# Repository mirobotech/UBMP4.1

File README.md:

# UBMP4.1

UBMP4.1 (USB-Based Beginner Multipurpose Project 4 rev. 1) KiCad schematic and PCB design files.

UBMP4.1 is a development board for learning or teaching PICmicro programming in C using almost any device – including Chromebooks!

## UBMP4.1 Hardware Features

- Microchip PIC16F1459 USB-capable microcontroller with 8k words of program FLASH (6k words free when using the USB bootloader), 128B of user FLASH, 1kB of RAM, 10-bit ADC, and a built-in temperature sensor
- 5 built-in pushbuttons
- 5 visible light LEDs
- 1 piezo beeper output
- optional 8-pin header for PORTC I/O pin expansion (great for servos, a SONAR module, NeoPixels, an LCD, etc.)
- optional IR LED output for remote control transmitter applications (or a high-current transistor-driven output)
- optional IR demodulator for remote control decoding
- optional IR phototransistor or visible-light ambient light sensor for light sensing
- USB 2.0 type-C port for power and programming
- 6-pin ICSP (In-Circuit Serial Programming) header for PICkit-4

## UBMP4.1 Software Features

UBMP4.1 uses the [USB uC](https://github.com/johnnydrazzi/USB-uC) bootloader, which makes UBMP4.1 appear as a USB mass storage device. Programs can be developed in C or assembly code using Microchip Technology's MPLAB X IDE or the MPLAB Xpress web-based IDE, or in any programming language or software that creates a Microchip-compatible .hex output file.

Just plug UBMP4.1 into a USB port, wait for it to appear on your computer as drive ***PIC16F1459***, and drag your compiled .hex file onto the drive. UMBP4.1 starts running your program as soon as the .hex file is transferred.

## UMBP4.1 is Open

UBMP4.1 is open hardware and uses open source software. The following permissions and conditions apply to UBMP4.1:
- the KiCad UBMP4.1 files stored in GitHub are open hardware licensed under the terms of the MIT license (except the mirobo.tech logo - see below)
- UBMP4.1 programs stored in GitHub are open source software licensed under the terms of the MIT license
- UMBP4.1 learning materials on the mirobo.tech website are licensed under the terms of the Creative Commons CC-BY 4.0 license
- the USB uC bootloader is open source and licensed under the terms of the GPL3.0 license by John Izzard
- the mirobo.tech logo mark is a trademark of mirobo Technolgy and may not be used without prior permission

## Where can I buy UBMP4.1?

UBMP4.1 boards and kits are available at [mirobo.tech](https://mirobo.tech/ubmp4).  
Bare UBMP4.1 printed circuit boards are also available from [OSHPARK](https://oshpark.com/shared_projects/b04AabPV).

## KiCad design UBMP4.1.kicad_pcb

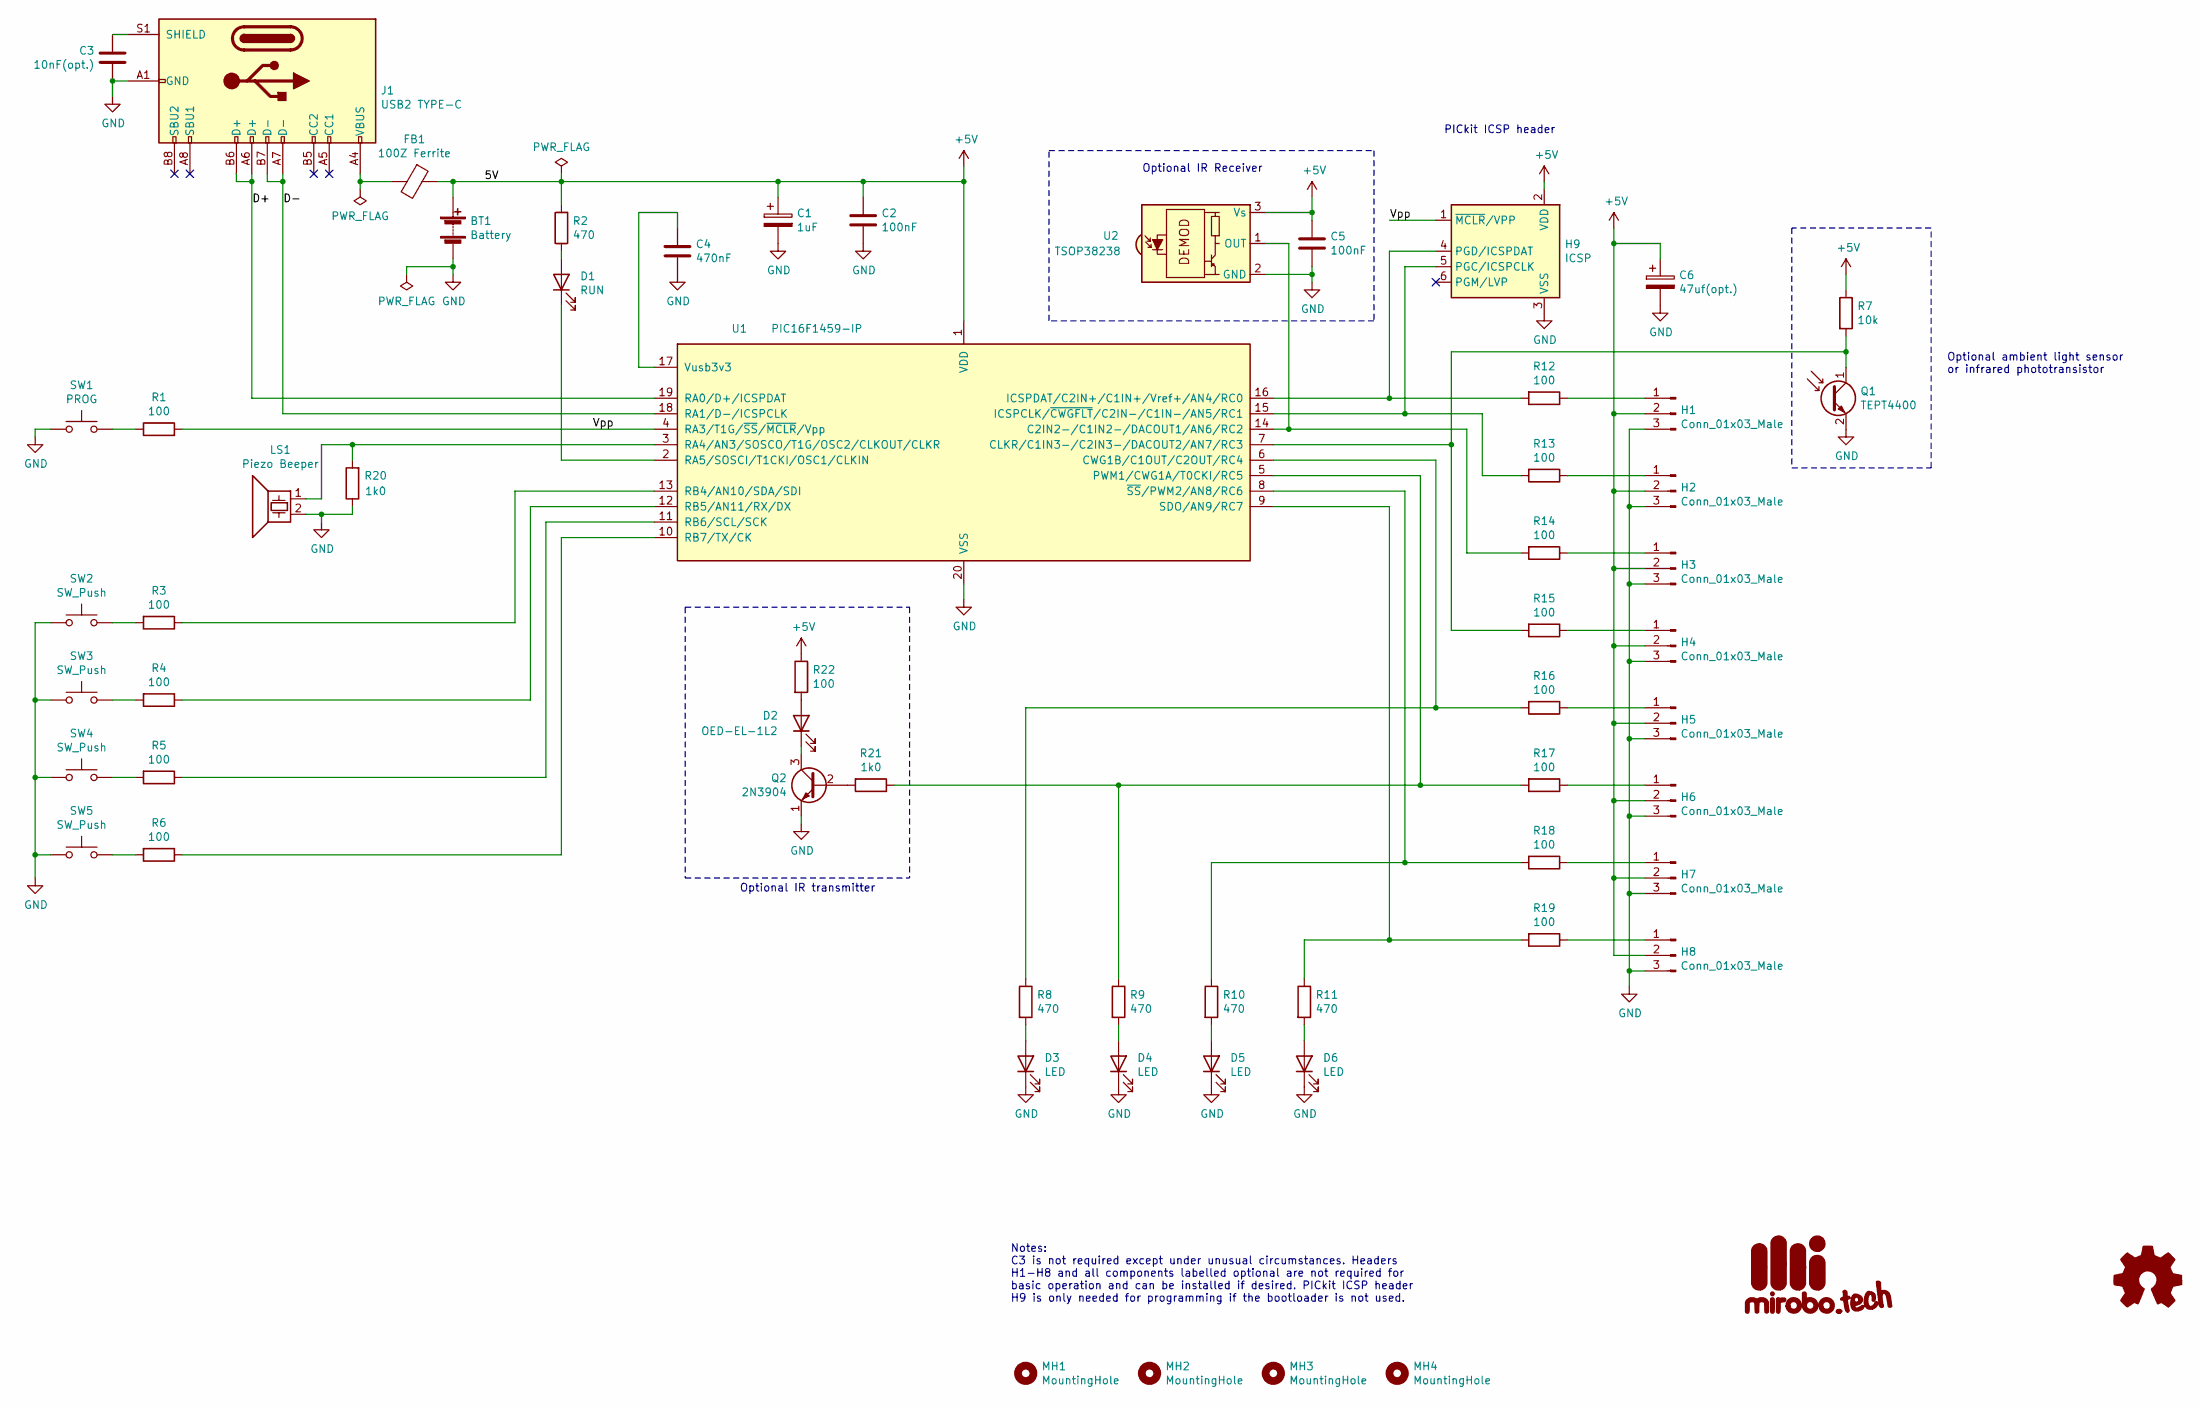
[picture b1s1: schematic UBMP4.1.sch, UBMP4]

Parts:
BT1: Battery; PinHeader_1x02_P2.54mm_Vertical
C1: 1uF; CP_Radial_D5.0mm_P2.50mm
C2, C5: 100nF; C_Disc_D3.4mm_W2.1mm_P2.50mm
C3: 10nF(opt.); C_Disc_D3.4mm_W2.1mm_P2.50mm
C4: 470nF; C_Disc_D3.4mm_W2.1mm_P2.50mm
C6: 47uf(opt.); CP_Radial_D6.3mm_P2.50mm
D1: RUN; LED_D3.0mm
D2: OED-EL-1L2; LED_D5.0mm_Horizontal_O1.27mm_Z3.0mm_Clear
D3, D4, D5, D6: LED; LED_D3.0mm
FB1: 100Z Ferrite; R_Axial_DIN0411_L9.9mm_D3.6mm_P12.70mm_Horizontal
G1: mirobotech_logo; mirobo_logo_10
G2: Logo_Open_Hardware_Small; OSHW-Symbol_6.7x6mm_SilkScreen
H1, H2, H3, H4, H5, H6, H7, H8: Conn_01x03_Male; PinHeader_1x03_P2.54mm_Vertical
H9: ICSP; PinHeader_1x06_P2.54mm_Horizontal
J1: USB2 TYPE-C; USB_C_Receptacle_GCT_USB4085
LS1: Piezo Beeper; Buzzer_TDK_PS1240P02BT_D12.2mm_H6.5mm
MH1, MH2, MH3, MH4: MountingHole; MountingHole_3.2mm_M3_Pad
Q1: TEPT4400; LED_D3.0mm_Clear
Q2: 2N3904; TO-92
R1, R3, R4, R5, R6, R12, R13, R14, R15, R16, R17, R18, R19, R22: 100; R_Axial_DIN0207_L6.3mm_D2.5mm_P10.16mm_Horizontal
R2, R8, R9, R10, R11: 470; R_Axial_DIN0207_L6.3mm_D2.5mm_P10.16mm_Horizontal
R7: 10k; R_Axial_DIN0207_L6.3mm_D2.5mm_P10.16mm_Horizontal
R20, R21: 1k0; R_Axial_DIN0207_L6.3mm_D2.5mm_P10.16mm_Horizontal
SW1: PROG; SW_PUSH_6mm
SW2, SW3, SW4, SW5: SW_Push; SW_PUSH_6mm
U1: PIC16F1459-IP; DIP-20_W7.62mm_Socket
U2: TSOP38238; Vishay_MINICAST-3Pin

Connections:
+5V: BT1.1 (+), C1.1, C2.1, C5.1, C6.1, FB1.1, H1.2, H2.2, H3.2, H4.2, H5.2, H6.2, H7.2, H8.2, H9.2 (VDD), R2.2, R7.1, R22.1, U1.1 (VDD), U2.3 (Vs)
/D+: J1.A6 (D+), J1.B6 (D+), U1.19 (RA0/D+/ICSPDAT)
/D-: J1.A7 (D-), J1.B7 (D-), U1.18 (RA1/D-/ICSPCLK)
/Vpp: H9.1 (~MCLR~/VPP), R1.2, U1.4 (RA3/T1G/~SS~/~MCLR~/Vpp)
GND: BT1.2 (-), C1.2, C2.2, C3.1, C4.2, C5.2, C6.2, D3.1 (K), D4.1 (K), D5.1 (K), D6.1 (K), H1.3, H2.3, H3.3, H4.3, H5.3, H6.3, H7.3, H8.3, H9.3 (VSS), J1.A1 (GND), J1.A12 (GND), J1.B1 (GND), J1.B12 (GND), LS1.2, Q1.2 (E), Q2.1 (E), R20.1, SW1.1, SW2.1, SW3.1, SW4.1, SW5.1, U1.20 (VSS), U2.2 (GND)
unnamed: C3.2, J1.S1 (SHIELD)
unnamed: C4.1, U1.17 (Vusb3v3)
unnamed: D1.1 (K), U1.2 (RA5/SOSCI/T1CKI/OSC1/CLKIN)
unnamed: D1.2 (A), R2.1
unnamed: D2.1 (K), Q2.3 (C)
unnamed: D2.2 (A), R22.2
unnamed: D3.2 (A), R8.2
unnamed: D4.2 (A), R9.2
unnamed: D5.2 (A), R10.2
unnamed: D6.2 (A), R11.2
unnamed: FB1.2, J1.A4 (VBUS), J1.A9 (VBUS), J1.B4 (VBUS), J1.B9 (VBUS)
unnamed: H1.1, R12.1
unnamed: H2.1, R13.1
unnamed: H3.1, R14.1
unnamed: H4.1, R15.1
unnamed: H5.1, R16.1
unnamed: H6.1, R17.1
unnamed: H7.1, R18.1
unnamed: H8.1, R19.1
unnamed: H9.4 (PGD/ICSPDAT), R12.2, U1.16 (ICSPDAT/C2IN+/C1IN+/Vref+/AN4/RC0)
unnamed: H9.5 (PGC/ICSPCLK), R13.2, U1.15 (ICSPCLK/~CWGFLT~/C2IN-/C1IN-/AN5/RC1)
unnamed: LS1.1, R20.2, U1.3 (RA4/AN3/SOSCO/T1G/OSC2/CLKOUT/CLKR)
unnamed: Q1.1 (C), R7.2, R15.2, U1.7 (CLKR/C1IN3-/C2IN3-/DACOUT2/AN7/RC3)
unnamed: Q2.2 (B), R21.2
unnamed: R1.1, SW1.2
unnamed: R3.1, U1.13 (RB4/AN10/SDA/SDI)
unnamed: R3.2, SW2.2
unnamed: R4.1, U1.12 (RB5/AN11/RX/DX)
unnamed: R4.2, SW3.2
unnamed: R5.1, U1.11 (RB6/SCL/SCK)
unnamed: R5.2, SW4.2
unnamed: R6.1, U1.10 (RB7/TX/CK)
unnamed: R6.2, SW5.2
unnamed: R10.1, R18.2, U1.8 (~SS~/PWM2/AN8/RC6)
unnamed: R11.1, R19.2, U1.9 (SDO/AN9/RC7)
unnamed: R14.2, U1.14 (C2IN2-/C1IN2-/DACOUT1/AN6/RC2), U2.1 (OUT)
unnamed: R8.1, R16.2, U1.6 (CWG1B/C1OUT/C2OUT/RC4)
unnamed: R9.1, R17.2, R21.1, U1.5 (PWM1/CWG1A/T0CKI/RC5)

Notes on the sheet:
Optional IR Receiver
Optional IR transmitter
PICkit ICSP header
Optional ambient light sensor or infrared phototransistor
Notes: C3 is not required except under unusual circumstances. Headers H1-H8 and all components labelled optional are not required for basic operation and can be installed if desired. PICkit ICSP header H9 is only needed for programming if the bootloader is not used.

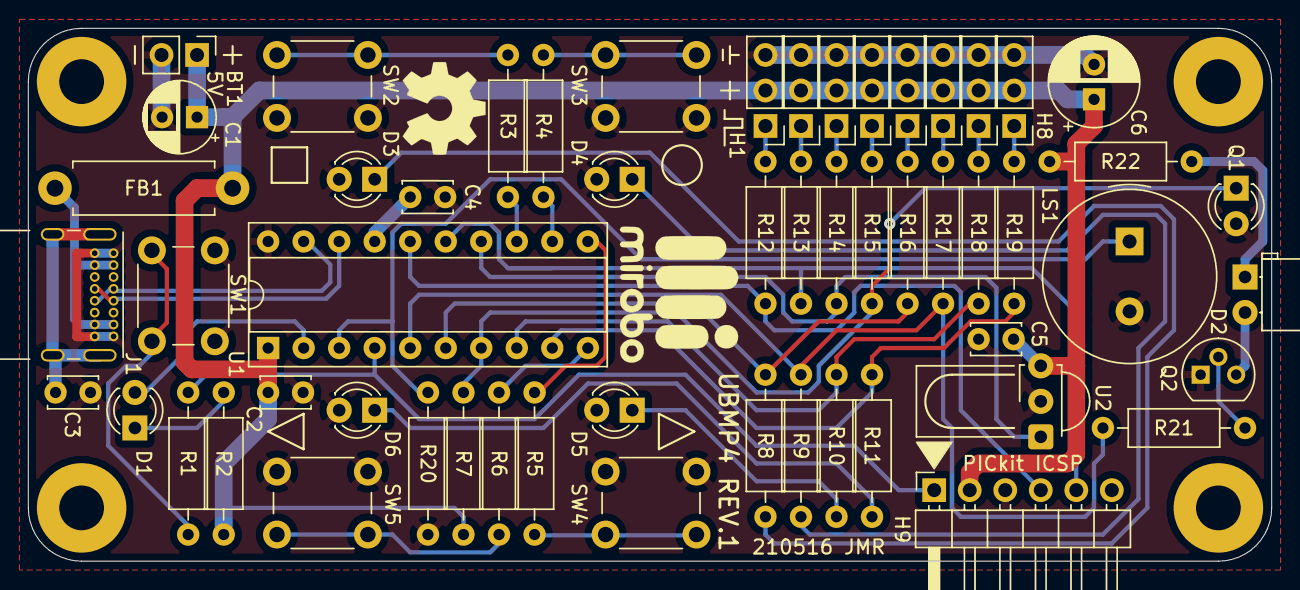
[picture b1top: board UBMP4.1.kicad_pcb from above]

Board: 2 copper layers, 88.9 x 38.1 mm, 62 parts (0 on the bottom side), 43 nets.

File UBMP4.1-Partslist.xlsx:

mirobo.tech UBMP4.1 Parts List
Item | Qty. | Reference(s) | Value | Description | Manuf. Part # | Digi-Key Part # | Datasheet
1 | 1 | UBMP4.1 PCB |  | UBMP4.1 printed circuit board | UBMP41 | ~ | ~
2 | 1 | BT1 | Solder contact (opt.) | Power lead solder pads or 0.1” connector |  | ~ | ~
3 | 1 | C1 | 1uF, 25V | Monolithic capacitor |  | 399-9714-ND | https://content.kemet.com/datasheets/KEM_C1050_GOLDMAX_X7R.pdf
4 | 2 | C2, C5 | 100nF, 100V | Monolithic capacitor |  | 399-9713-ND | https://content.kemet.com/datasheets/KEM_C1050_GOLDMAX_X7R.pdf
5 | 1 | C3 | 10nF, 50V (opt.) | Monolithic capacitor |  | 399-4148-ND | https://content.kemet.com/datasheets/KEM_C1050_GOLDMAX_X7R.pdf
6 | 1 | C4 | 470nF, 50V | Monolithic capacitor |  | 399-9741-ND | https://content.kemet.com/datasheets/KEM_C1050_GOLDMAX_X7R.pdf
7 | 1 | C6 | 47uf, 16V (opt.) | Electrolytic capacitor |  |  | ~
8 | 1 | D1 | 3mm LED | Program/Run LED | LTL-4232N | 160-1143-ND | ~
9 | 1 | D2 | IR LED (opt.) | Lumex IR LED for IR remote control transmission | OED-EL-1L2 | 67-1001-ND | https://www.lumex.com/datasheet/OED-EL-1L2
10 | 4 | D3, D4, D5, D6 | 3mm LED | User I/O LEDs | LTL-4251N | 160-1145-ND | ~
12 | 1 | FB1 | 100Z ferrite bead | Laird ferrite bead 100Ω @ 25 MHz | 28L0138-40R-10 | 28L0138-40R-10 240-2439-1-ND | https://media.digikey.com/pdf/Data%20Sheets/Laird%20Technolo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
13 | 8 | H1, H2, H3, H4, H5, H6, H7, H8 | 01x03 0.1” pin header (opt.) | I/O header posts for servos, external modules | PBC36SAAN | S1011E-36-ND | ~
15 | 1 | H9 | 01x06 0.1” RA pin header (opt.) | PICkit ICSP programming header | PBC36SBAN | S1111E-36-ND | http://ww1.microchip.com/downloads/en/devicedoc/30277d.pdf
16 | 1 | J1 | USB2 TYPE-C | GCT USB2 Type-C power/prog. connector | USB4085-GF-A | 2073-USB4085-GF-ACT-ND | https://media.digikey.com/pdf/Data%20Sheets/GCT%20PDFs/Ionex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
17 | 1 | LS1 | Piezo beeper | TDK 12.2mm piezo audio transducer | PS1240P02BT | 445-2525-1-ND | ~
18A | 1 | Q1 | Ambient light sensor (opt.) | Vishay ambient light sensor | TEPT4400 | 751-1057-ND | https://www.vishay.com/docs/81341/tept4400.pdf
18B | 1 | Q1 | IR phototransistor (opt.) | Lite-On IR phototransistor | LTR-4206E | 160-1030-ND | https://optoelectronics.liteon.com/upload/download/DS-50-92-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
19 | 1 | Q2 | 2N3904 | NPN transistor | 2N3904 (generic) | 2N3904FS-ND | https://www.onsemi.com/pdf/datasheet/pzt3904-d.pdf
20 | 14 | R1, R3, R4, R5, R6, R12, R13, R14, R15, R16, R17, R18, R19, R22 | 100Ω, 1/4W | 5% carbon film resistor | 100Ω (generic) | 100QBK-ND | ~
21 | 5 | R2, R8, R9, R10, R11 | 470Ω, 1/4W | 5% carbon film resistor | 470Ω (generic) | 470QBK-ND | ~
22 | 1 | R7 | 10kΩ, 1/4W | 5% carbon film resistor | 10kΩ (generic) | 10KQBK-ND | ~
24 | 2 | R20, R21 | 1k0Ω, 1/4W | 5% carbon film resistor | 1.0kΩ (generic) | 1.0KQBK-ND | ~
25 | 5 | SW1, SW2, SW3, SW4, SW5 | 6mm pushbutton | Omron 6mm momentary pushbutton | B3F-1000 | SW400-ND | ~
26 | 1 | U1 | PIC16F1459-I/P | Microchip Technology PIC16F1459 USB-capable microcontroller | PIC16F1459-I/P | PIC16F1459-I/P-ND | https://www.microchip.com/wwwproducts/en/PIC16F1459
27 | 1 | U2 | TSOP38238 (opt.) | Vishay 38kHz IR demodulator | TSOP38238 | 751-1227-ND | http://www.vishay.com/docs/82491/tsop382.pdf
 | 58 | Total Components

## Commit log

2021-06-06 Initial Release
2021-06-06 Updated .gitignore
2021-06-06 Update Readme.

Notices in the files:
UBMP4.1.sch:
Schematic: CC-BY 4.0
